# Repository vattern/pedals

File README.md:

# pedals
KiCad layouts for pedals

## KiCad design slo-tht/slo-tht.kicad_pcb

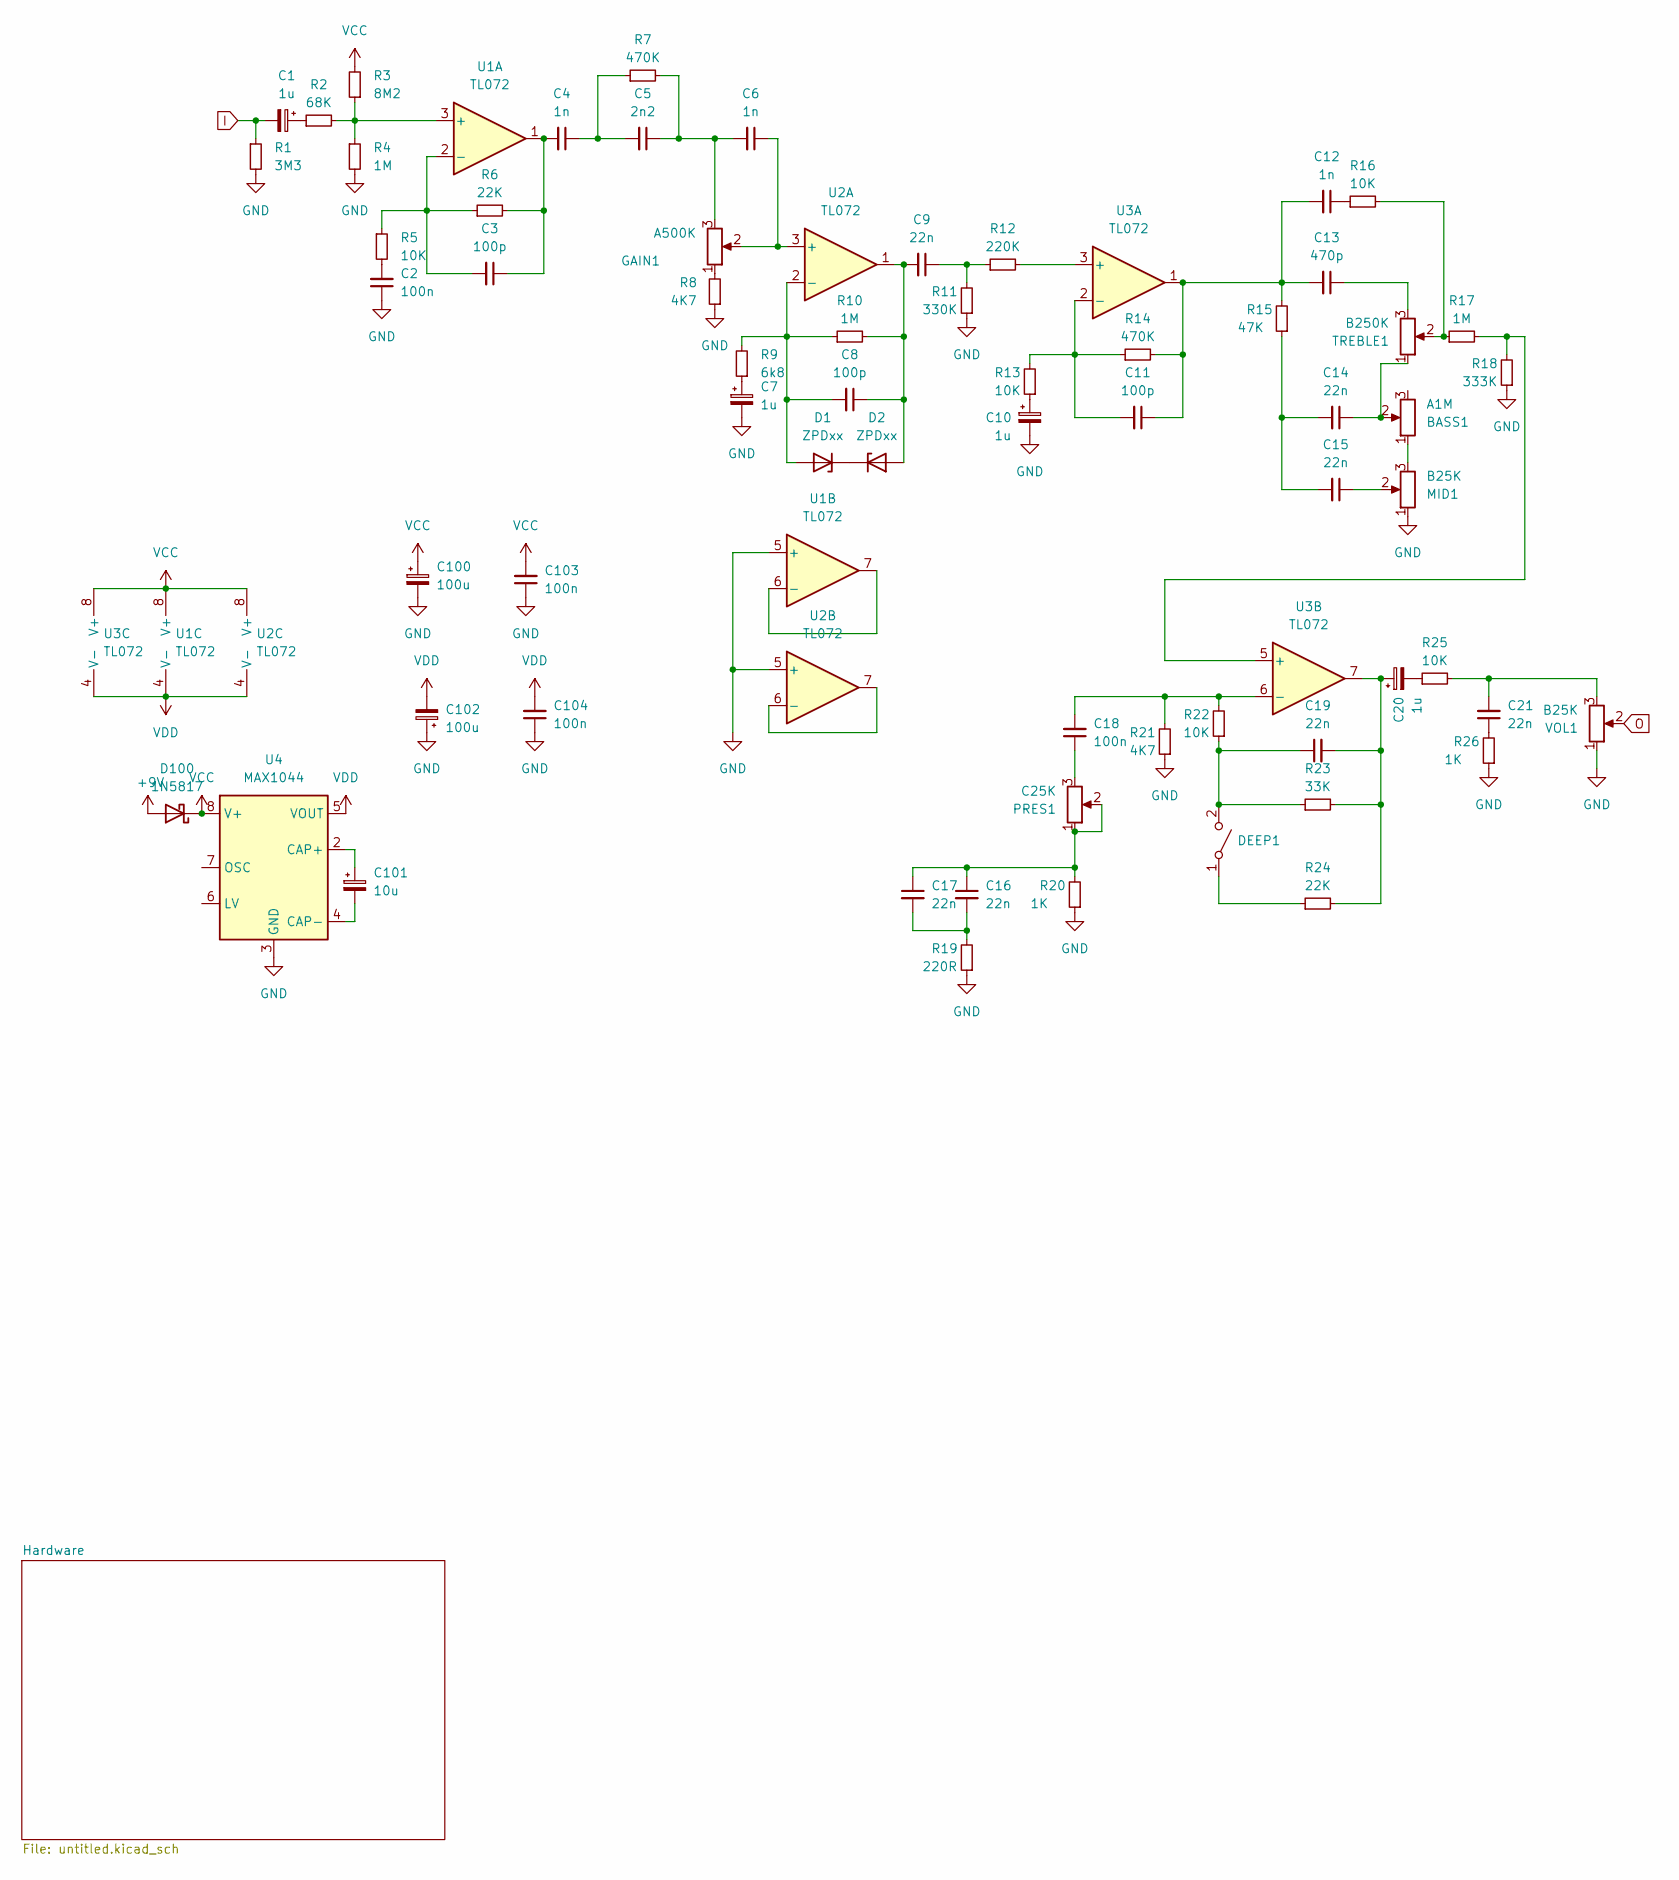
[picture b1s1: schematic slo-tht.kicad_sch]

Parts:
BASS1: A1M; Potentiometer_Alpha_RD901F-40-00D_Single_Vertical_copy
C1, C7, C10, C20: 1u; CP_Radial_D5.0mm_P2.50mm; JLCC C445065
C2, C18, C103, C104: 100n; C_Rect_L7.0mm_W2.5mm_P5.00mm; JLCC C531430
C3, C8, C11: 100p; C_Rect_L7.0mm_W2.5mm_P5.00mm; JLCC C1790
C4, C6, C12: 1n; C_Rect_L7.0mm_W2.5mm_P5.00mm; JLCC C1791
C5: 2n2; C_Rect_L7.0mm_W2.5mm_P5.00mm; JLCC C28260
C9, C14, C15, C16, C17, C19, C21: 22n; C_Rect_L7.0mm_W2.5mm_P5.00mm; JLCC C77069
C13: 470p; C_Rect_L7.0mm_W2.5mm_P5.00mm; JLCC C76630
C100, C102: 100u; CP_Radial_D8.0mm_P2.50mm; JLCC C178548
C101: 10u; CP_Radial_D5.0mm_P2.50mm; JLCC C128456
D1, D2: ZPDxx; D_DO-34_SOD68_P7.62mm_Horizontal
D100: 1N5817; D_DO-34_SOD68_P7.62mm_Horizontal; LCSC C727113
DEEP1: SW_Toggle_Blue_wSlots
GAIN1: A500K; Potentiometer_Alpha_RD901F-40-00D_Single_Vertical_copy
MID1: B25K; Potentiometer_Alpha_RD901F-40-00D_Single_Vertical_copy
PRES1: C25K; Potentiometer_Alpha_RD901F-40-00D_Single_Vertical_copy
R1: 3M3; R_Axial_DIN0204_L3.6mm_D1.6mm_P7.62mm_Horizontal; LCSC C137436
R2: 68K; R_Axial_DIN0204_L3.6mm_D1.6mm_P7.62mm_Horizontal; LCSC C17801
R3: 8M2; R_Axial_DIN0204_L3.6mm_D1.6mm_P7.62mm_Horizontal; LCSC C141694
R4: 1M; R_Axial_DIN0204_L3.6mm_D1.6mm_P7.62mm_Horizontal; JLCC C17514
R5, R13, R16, R22, R25: 10K; R_Axial_DIN0204_L3.6mm_D1.6mm_P7.62mm_Horizontal; LCSC C17414
R6, R24: 22K; R_Axial_DIN0204_L3.6mm_D1.6mm_P7.62mm_Horizontal; LCSC C17560
R7, R14: 470K; R_Axial_DIN0204_L3.6mm_D1.6mm_P7.62mm_Horizontal
R8, R21: 4K7; R_Axial_DIN0204_L3.6mm_D1.6mm_P7.62mm_Horizontal
R9: 6k8; R_Axial_DIN0204_L3.6mm_D1.6mm_P7.62mm_Horizontal
R10, R17: 1M; R_Axial_DIN0204_L3.6mm_D1.6mm_P7.62mm_Horizontal; LCSC C17514
R11: 330K; R_Axial_DIN0204_L3.6mm_D1.6mm_P7.62mm_Horizontal
R12: 220K; R_Axial_DIN0204_L3.6mm_D1.6mm_P7.62mm_Horizontal
R15: 47K; R_Axial_DIN0204_L3.6mm_D1.6mm_P7.62mm_Horizontal
R18: 333K; R_Axial_DIN0204_L3.6mm_D1.6mm_P7.62mm_Horizontal
R19: 220R; R_Axial_DIN0204_L3.6mm_D1.6mm_P7.62mm_Horizontal
R20: 1K; R_Axial_DIN0204_L3.6mm_D1.6mm_P7.62mm_Horizontal; JLCC C17513
R23: 33K; R_Axial_DIN0204_L3.6mm_D1.6mm_P7.62mm_Horizontal
R26: 1K; R_Axial_DIN0204_L3.6mm_D1.6mm_P7.62mm_Horizontal; LCSC C17513
TREBLE1: B250K; Potentiometer_Alpha_RD901F-40-00D_Single_Vertical_copy
U1, U2, U3: TL072; DIP-8_W7.62mm
U4: MAX1044; DIP-8_W7.62mm; JLCC C7028
VOL1: B25K; Potentiometer_Alpha_RD901F-40-00D_Single_Vertical_copy

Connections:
+9V: D100.2 (A); also elsewhere on the board
GND: C2.1, C7.2, C10.2, C100.2, C102.1, C103.1, C104.1, MID1.1, R1.2, R4.2, R8.1, R11.1, R18.1, R19.1, R20.1, R21.1, R26.1, U1.5 (+), U2.5 (+), U4.3 (GND), VOL1.1; also elsewhere on the board
I: C1.2, R1.1; also elsewhere on the board
unnamed: BASS1.1, MID1.3
unnamed: BASS1.2, C14.1, TREBLE1.1
unnamed: C1.1, R2.1
unnamed: C2.2, R5.2
unnamed: C3.1, C4.2, R6.2, U1.1
unnamed: C4.1, C5.2, R7.1
unnamed: C5.1, C6.2, GAIN1.3, R7.2
unnamed: C7.1, R9.1
unnamed: C9.1, R11.2, R12.1
unnamed: C10.1, R13.1
unnamed: C11.1, C12.2, C13.2, R14.2, R15.2, U3.1
unnamed: C12.1, R16.1
unnamed: C13.1, TREBLE1.3
unnamed: C14.2, C15.2, R15.1
unnamed: C15.1, MID1.2
unnamed: C16.1, C17.1, PRES1.1, PRES1.2, R20.2
unnamed: C16.2, C17.2, R19.2
unnamed: C18.1, PRES1.3
unnamed: C19.2, C20.1, R23.2, R24.2, U3.7
unnamed: C20.2, R25.1
unnamed: C21.1, R26.2
unnamed: C21.2, R25.2, VOL1.3
unnamed: C8.2, D1.2 (A), R9.2, R10.1, U2.2 (-)
unnamed: D1.1 (K), D2.1 (K)
unnamed: C8.1, C9.2, D2.2 (A), R10.2, U2.1
unnamed: DEEP1.1 (A), R24.1
unnamed: C19.1, DEEP1.2 (B), R22.1, R23.1
unnamed: GAIN1.1, R8.2
unnamed: R16.2, R17.1, TREBLE1.2
unnamed: R2.2, R3.1, R4.1, U1.3 (+)
unnamed: C3.2, R5.1, R6.1, U1.2 (-)
unnamed: U1.6 (-), U1.7
unnamed: C6.1, GAIN1.2, U2.3 (+)
unnamed: U2.6 (-), U2.7
unnamed: R12.2, U3.3 (+)
unnamed: C11.2, R13.2, R14.1, U3.2 (-)
unnamed: R17.2, R18.2, U3.5 (+)
unnamed: C18.2, R21.2, R22.2, U3.6 (-)
unnamed: C101.1, U4.2 (CAP+)
unnamed: C101.2, U4.4 (CAP-)
O: VOL1.2; also elsewhere on the board
VCC: C100.1, C103.2, D100.1 (K), R3.2, U1.8 (V+), U2.8 (V+), U3.8 (V+), U4.8 (V+)
VDD: C102.2, C104.2, U1.4 (V-), U2.4 (V-), U3.4 (V-), U4.5 (VOUT)

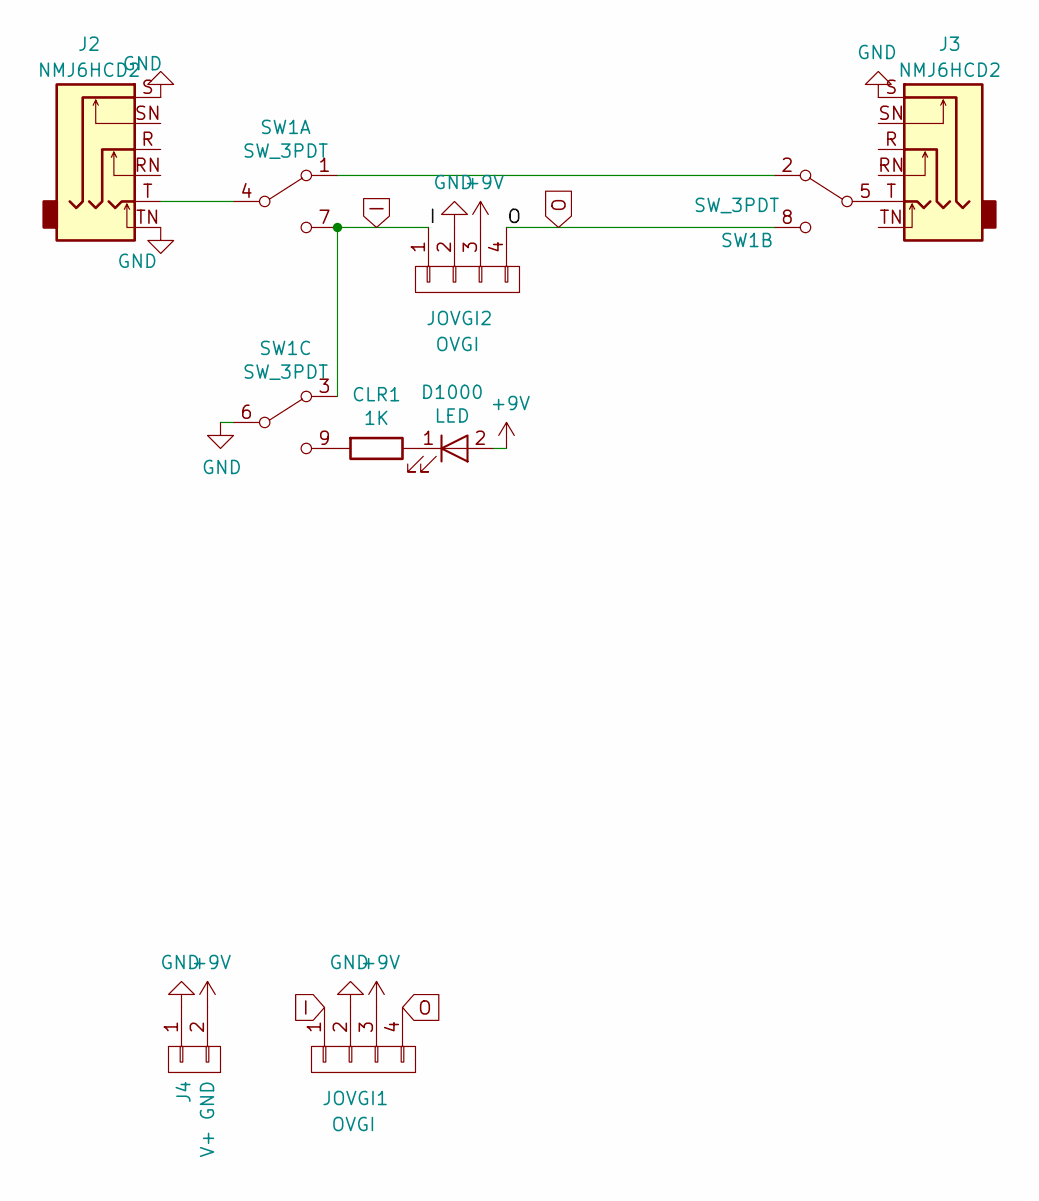
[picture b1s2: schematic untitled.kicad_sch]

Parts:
CLR1: 1K; R_Axial_DIN0204_L3.6mm_D1.6mm_P7.62mm_Horizontal
D1000: LED; LED-5MM
J2, J3: NMJ6HCD2; Jack_6.35mm_Neutrik_NMJ6HCD2_Horizontal
J4: V+ GND; PinHeader_1x02_P2.54mm_Vertical
JOVGI1, JOVGI2: OVGI; Pin_Header_Straight_1x04_Pitch2.54mm
SW1: SW_3PDT; 3PDT-Footswitch

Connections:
+9V: D1000.2 (A), J4.2, JOVGI1.3, JOVGI2.3; also elsewhere on the board
GND: J2.S, J2.TN, J3.S, J4.1, JOVGI1.2, JOVGI2.2, SW1.6 (B); also elsewhere on the board
I: JOVGI1.1, JOVGI2.1, SW1.3 (A), SW1.7 (C); also elsewhere on the board
unnamed: CLR1.1, D1000.1 (K)
unnamed: SW1.1 (A), SW1.2 (A)
unnamed: J2.T, SW1.4 (B)
unnamed: J3.T, SW1.5 (B)
unnamed: CLR1.2, SW1.9 (C)
O: JOVGI1.4, JOVGI2.4, SW1.8 (C); also elsewhere on the board

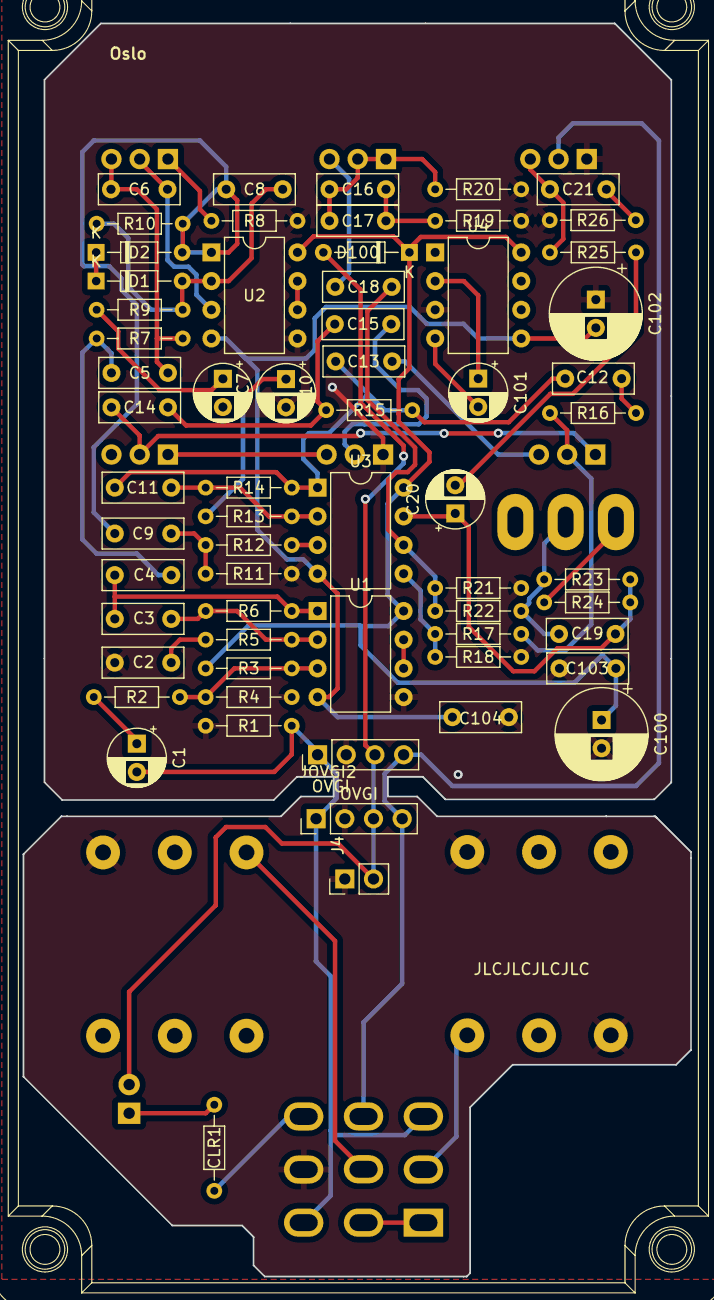
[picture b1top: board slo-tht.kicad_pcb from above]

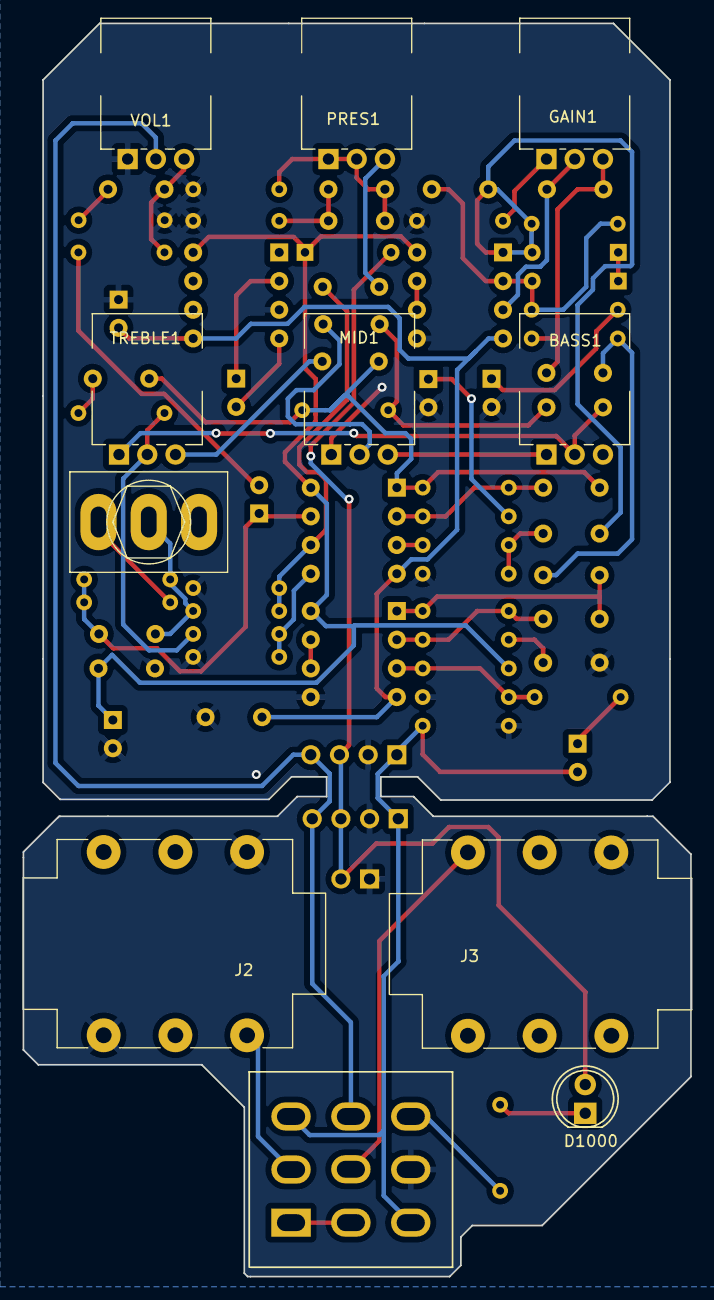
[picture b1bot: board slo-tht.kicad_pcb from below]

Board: 2 copper layers, 59.1 x 110.9 mm, 74 parts (11 on the bottom side), 51 nets.

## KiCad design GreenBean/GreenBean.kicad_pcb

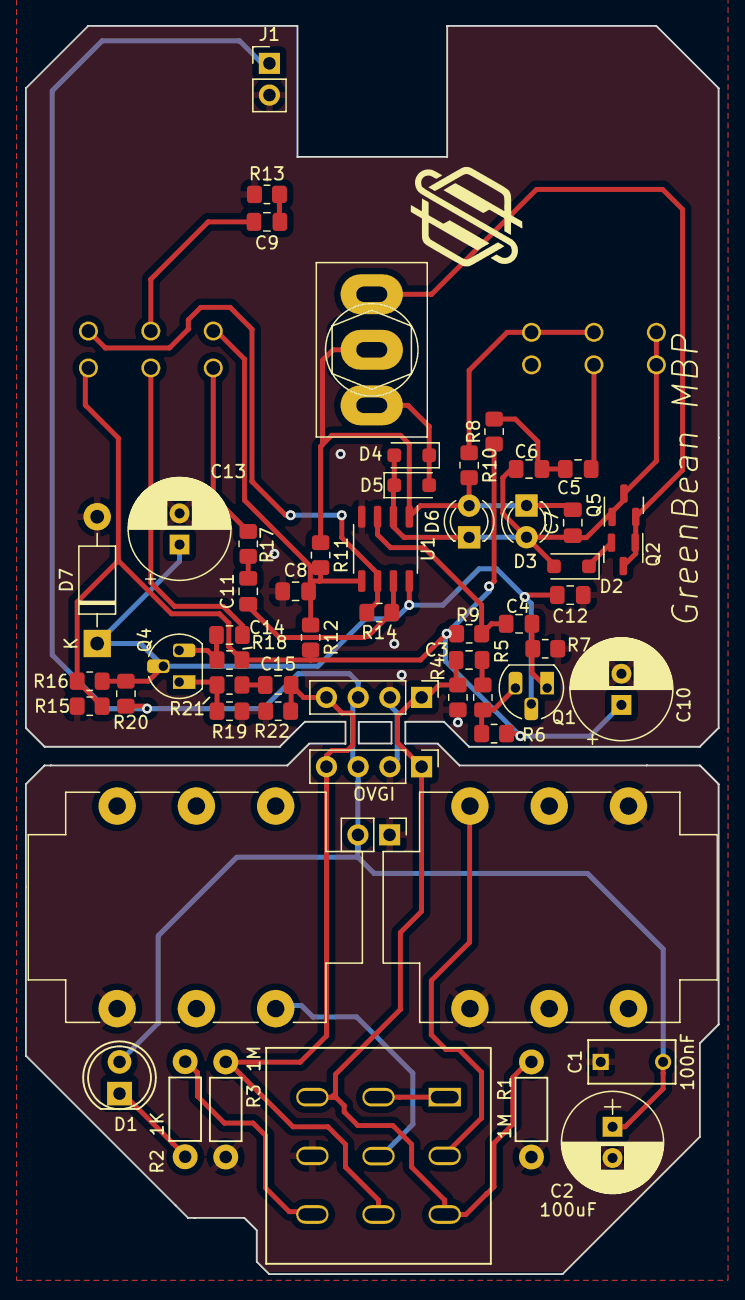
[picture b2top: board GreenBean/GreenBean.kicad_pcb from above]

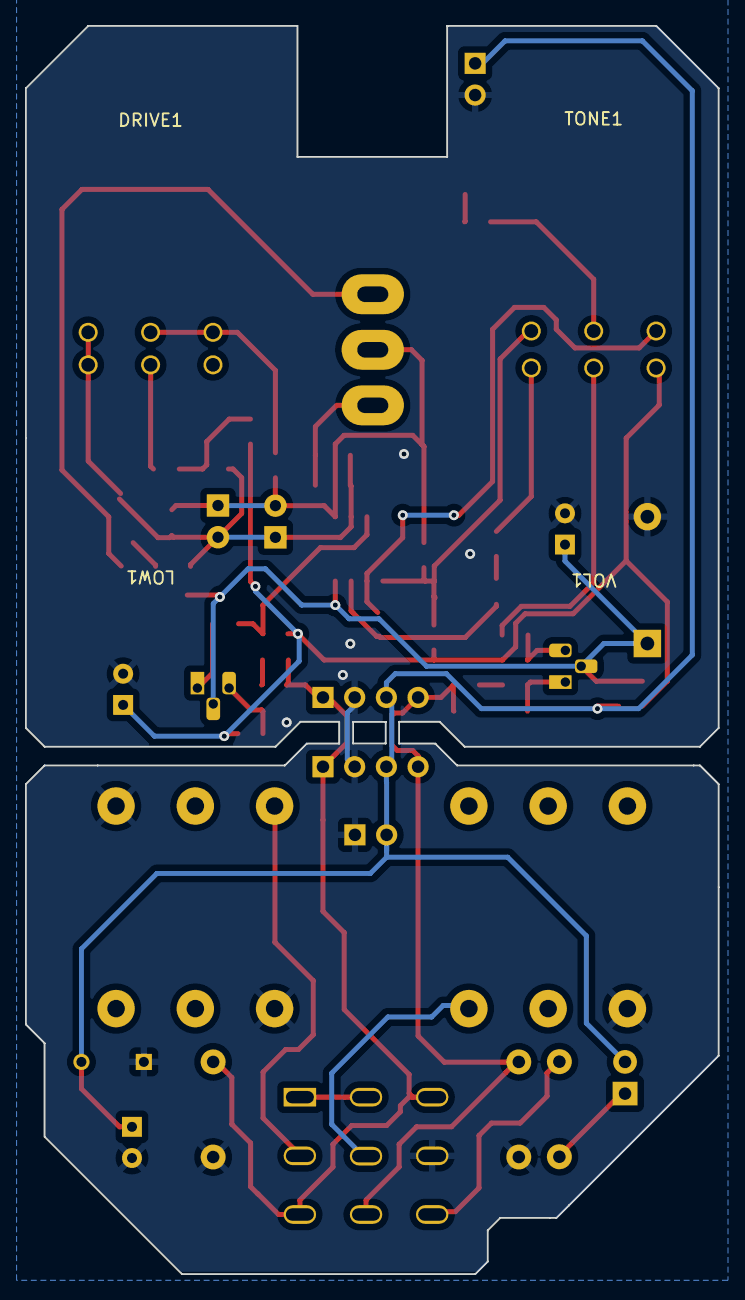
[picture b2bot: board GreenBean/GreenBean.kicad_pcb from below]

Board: 2 copper layers, 55.5 x 100.0 mm, 62 parts (4 on the bottom side), 34 nets.

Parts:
C1: 100nF; C_Rect_L7_W3.5_P5
C2, C13: 100uF; CP_Radial_D8.0mm_P2.50mm
C3: 20n; C_0805_2012Metric_Pad1.18x1.45mm_HandSolder
C4, C11, C15: 1u; C_0805_2012Metric_Pad1.18x1.45mm_HandSolder
C5: 150n; C_0805_2012Metric_Pad1.18x1.45mm_HandSolder
C6: 47n; C_0805_2012Metric_Pad1.18x1.45mm_HandSolder
C7: 51p; C_0805_2012Metric_Pad1.18x1.45mm_HandSolder
C8, C9, C12: 220n; C_0805_2012Metric_Pad1.18x1.45mm_HandSolder
C10: 10uF; CP_Radial_D8.0mm_P2.50mm
C14: 100n; C_0805_2012Metric_Pad1.18x1.45mm_HandSolder
D1: LED; LED-5MM
D2: BAT41; D_SOD-123F
D3, D6: LED; LED_D3.0mm
D4, D5: 1N914; D_SOD-123F
D7: 1N4001; D_DO-41_SOD81_P10.16mm_Horizontal
DRIVE1: 500KA; Potentiometer_ALPHA_RV16106N
J1, J4: V+ GND; PinHeader_1x02_P2.54mm_Vertical
J2, J3: NMJ6HCD2; Jack_6.35mm_Neutrik_NMJ6HCD2_Horizontal
JOVGI1, JOVGI2: OVGI; Pin_Header_Straight_1x04_Pitch2.54mm
LOW1: 20KB; Potentiometer_ALPHA_RV16106N
N1: Housing; 1590B
Q1, Q4: 2SC1815; TO-92L_HandSolder
Q2, Q5: 2N7002; SOT-23
R1, R3: 1M; Resistor_Horizontal_RM7mm
R2: 1K; Resistor_Horizontal_RM7mm
R4: 1M; R_0805_2012Metric_Pad1.20x1.40mm_HandSolder
R5, R11, R14, R17: 1k; R_0805_2012Metric_Pad1.20x1.40mm_HandSolder
R6, R18: 510k; R_0805_2012Metric_Pad1.20x1.40mm_HandSolder
R7, R9, R12, R15, R16, R19, R22: 10k; R_0805_2012Metric_Pad1.20x1.40mm_HandSolder
R8: 4k7; R_0805_2012Metric_Pad1.20x1.40mm_HandSolder
R10: 51k; R_0805_2012Metric_Pad1.20x1.40mm_HandSolder
R13: 220R; R_0805_2012Metric_Pad1.20x1.40mm_HandSolder
R20: 47R; R_0805_2012Metric_Pad1.20x1.40mm_HandSolder
R21: 100R; R_0805_2012Metric_Pad1.20x1.40mm_HandSolder
SW1: SW_3PDT; 3PDT-Footswitch
SW2: SW_SPDT; SW_Toggle_Blue_wSlots
TONE1: 20KB; Potentiometer_ALPHA_RV16106N
U1: RC4558; SO-8_3.9x4.9mm_P1.27mm
VOL1: 100KB; Potentiometer_ALPHA_RV16106N

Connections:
+9V: C1.2, C2.1, D1.2 (A), J1.1, J4.2, JOVGI1.3, JOVGI2.3, R20.2
A: C6.2, C7.1, D2.2 (A), D3.2 (A), D4.2 (A), D5.1 (K), D6.1 (K), DRIVE1.1, LOW1.3, Q5.1 (G), Q5.3 (D), U1.2 (-)
B: C7.2, D3.1 (K), D6.2 (A), R10.2, R11.1, SW2.2, U1.1
GND: C1.1, C2.2, C8.1, C10.2, C12.1, C13.2, D7.2 (A), J1.2, J2.S, J2.TN, J3.S, J4.1, JOVGI1.2, JOVGI2.2, R1.2, R3.2, R4.1, R7.1, R13.1, R15.1, R19.1, R22.1, SW1.6 (B), U1.4 (V-)
I: C3.1, JOVGI1.1, JOVGI2.1, R1.1, R4.2, SW1.3 (A), SW1.7 (C)
unnamed: C3.2, R5.2
unnamed: C5.1, C6.1, R8.2
unnamed: C5.2, LOW1.2
unnamed: C9.1, R13.2
unnamed: C9.2, TONE1.2
unnamed: C11.1, R14.2, U1.7
unnamed: C11.2, R17.1
unnamed: C14.1, VOL1.2
unnamed: C15.1, R21.2
unnamed: D1.1 (K), R2.1
unnamed: D2.1 (K), Q2.2 (S)
unnamed: D4.1 (K), D5.2 (A), SW2.1
unnamed: DRIVE1.2, DRIVE1.3, R10.1
unnamed: Q1.3 (B), R5.1, R6.1
unnamed: C4.1, Q1.1 (E), R7.2
unnamed: Q2.1 (G), Q2.3 (D), Q5.2 (S), SW2.3
unnamed: C14.2, Q4.3 (B), R18.1
unnamed: Q4.1 (E), R19.2, R21.1
unnamed: R17.2, VOL1.3
unnamed: SW1.1 (A), SW1.2 (A)
unnamed: J2.T, SW1.4 (B)
unnamed: J3.T, SW1.5 (B)
unnamed: R2.2, SW1.9 (C)
unnamed: C4.2, R9.1, U1.3 (+)
unnamed: C8.2, R11.2, R12.1, TONE1.1, U1.5 (+)
unnamed: R14.1, TONE1.3, U1.6 (-)
O: C15.2, JOVGI1.4, JOVGI2.4, R3.1, R22.2, SW1.8 (C)
VB: C10.1, R6.2, R8.1, R9.2, R12.2, R15.2, R16.1, R18.2, VOL1.1
VC: C12.2, C13.1, D7.1 (K), Q1.2 (C), Q4.2 (C), R16.2, R20.1, U1.8 (V+)

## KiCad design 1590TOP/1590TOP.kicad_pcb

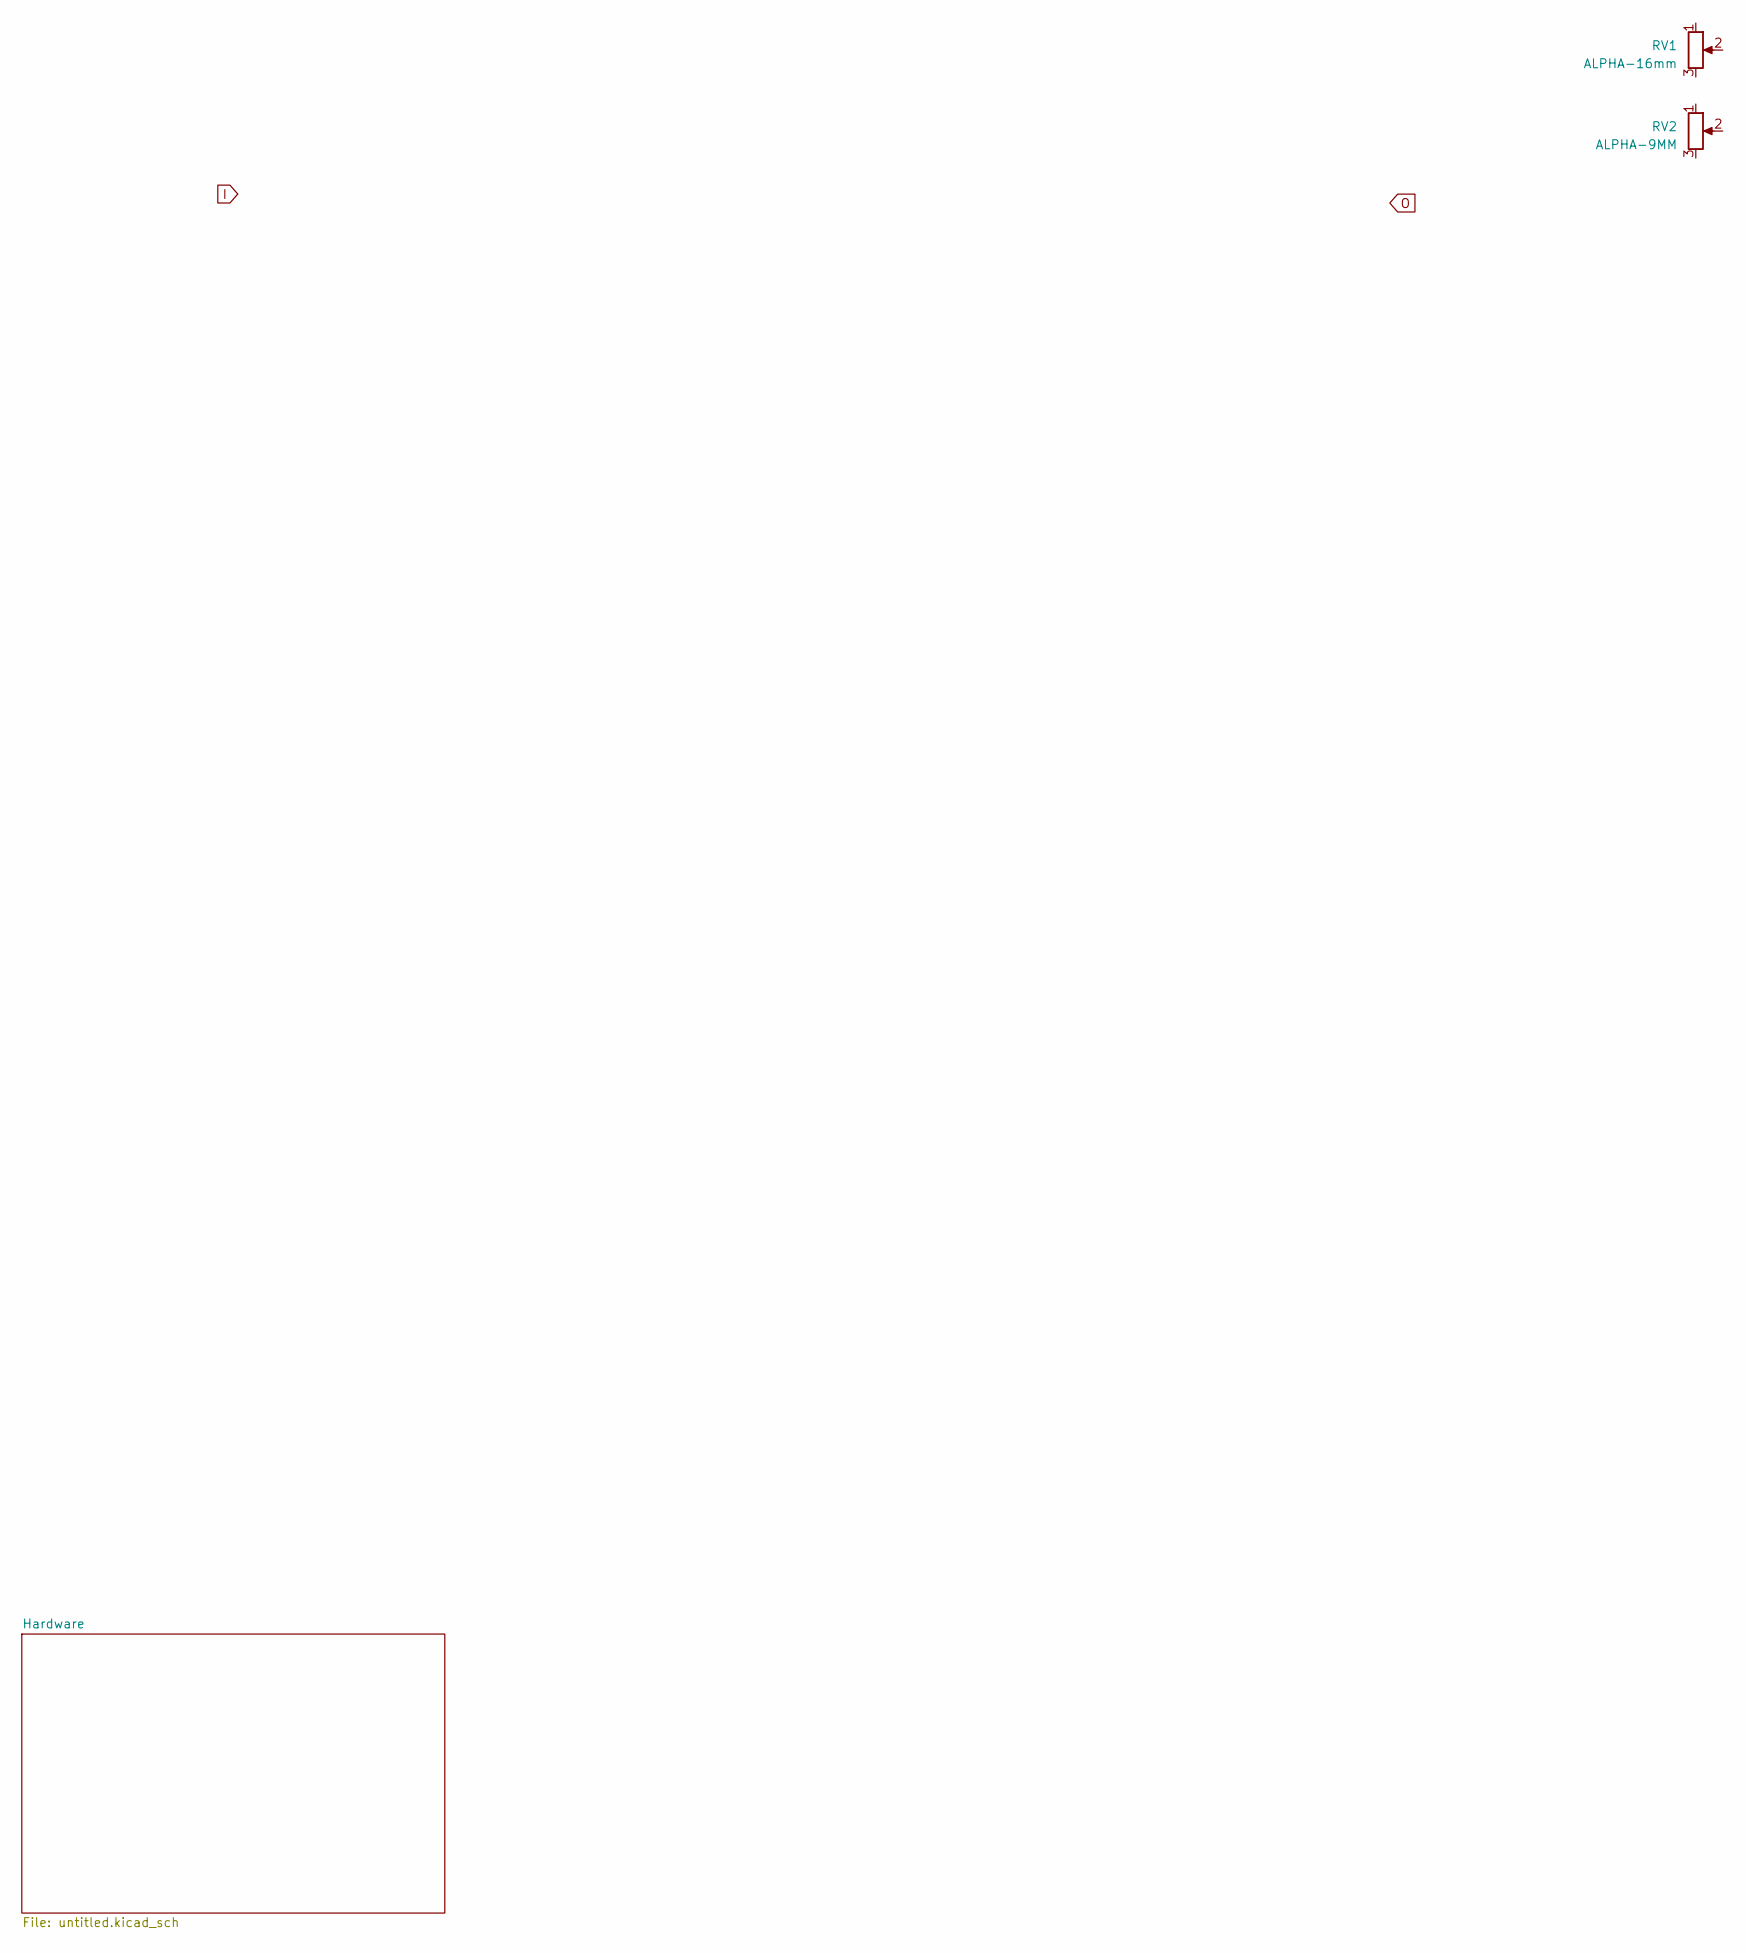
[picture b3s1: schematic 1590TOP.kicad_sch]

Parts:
RV1: ALPHA-16mm; Potentiometer_ALPHA_RV16106N
RV2: ALPHA-9MM; Potentiometer_Alpha_RD901F-40-00D_Single_Vertical

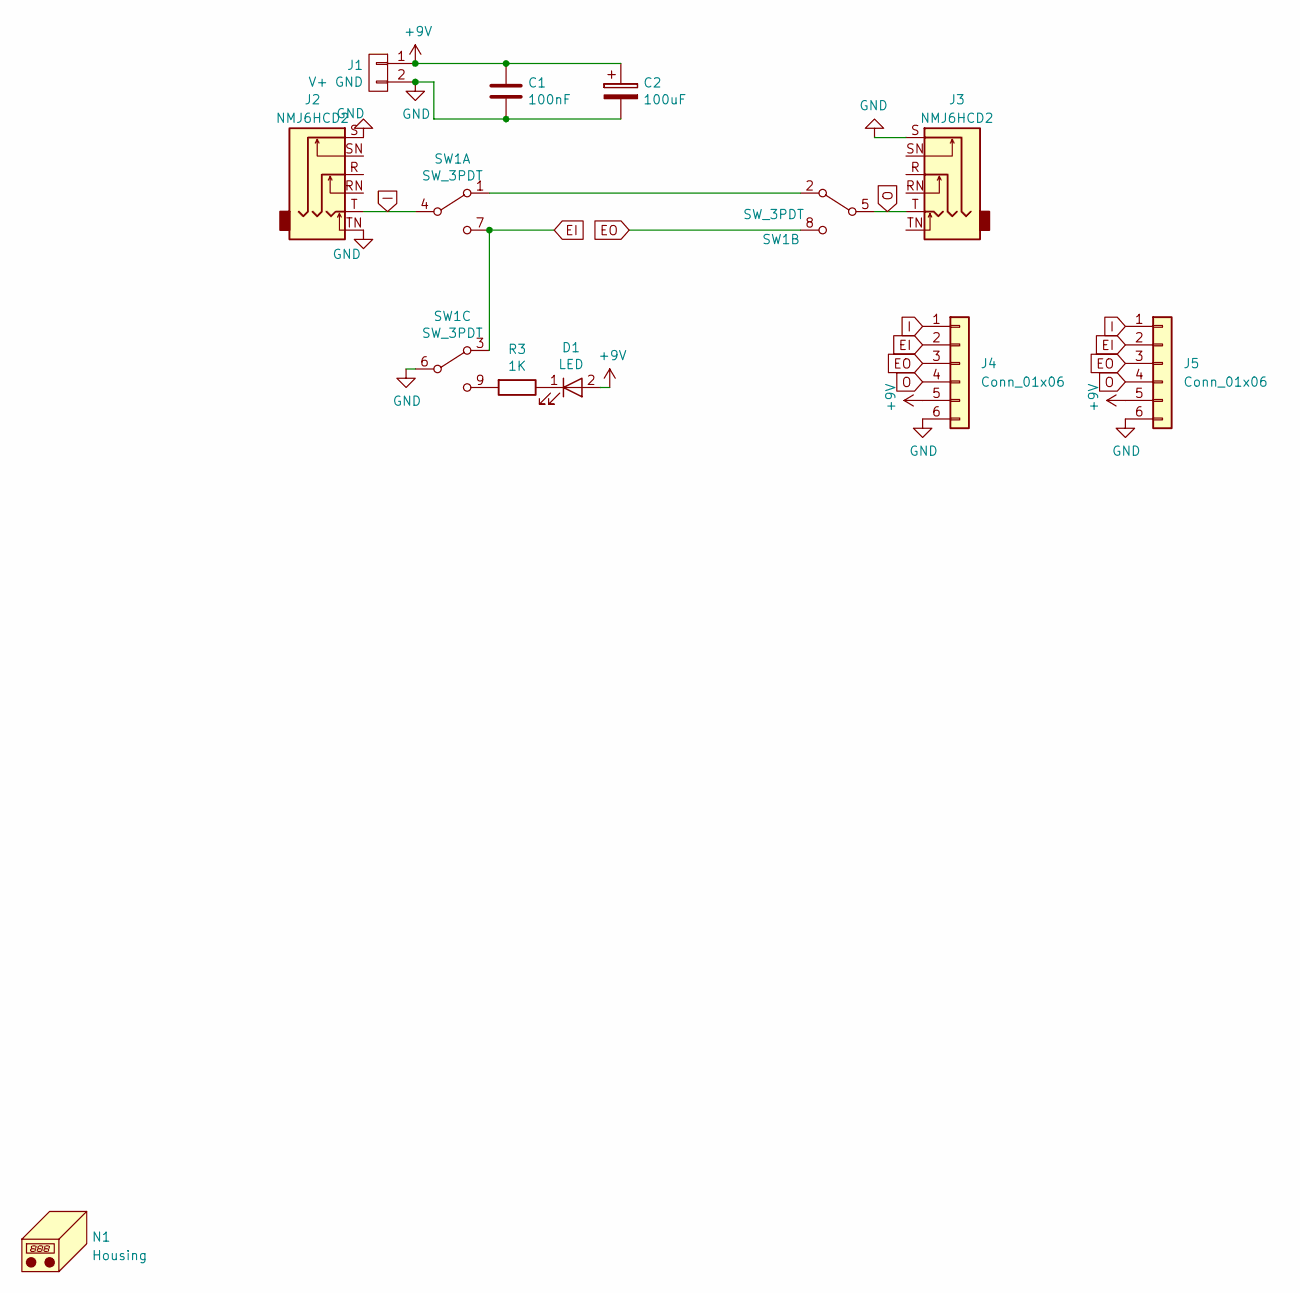
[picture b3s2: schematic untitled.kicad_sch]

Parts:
C1: 100nF; C_Rect_L7_W3.5_P5
C2: 100uF; CP_Radial_D8.0mm_P2.50mm
D1: LED; LED-5MM
J1: V+ GND; PinHeader_1x02_P2.54mm_Vertical
J2, J3: NMJ6HCD2; Jack_6.35mm_Neutrik_NMJ6HCD2_Horizontal
J4, J5: Conn_01x06; PinHeader_1x06_P2.54mm_Vertical
N1: Housing; 1590B
R3: 1K; Resistor_Horizontal_RM7mm
SW1: SW_3PDT; 3PDT-Footswitch

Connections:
+9V: C1.2, C2.1, D1.2 (A), J1.1, J4.5, J5.5
EI: J4.2, J5.2, SW1.3 (A), SW1.7 (C)
EO: J4.3, J5.3, SW1.8 (C)
GND: C1.1, C2.2, J1.2, J2.S, J2.TN, J3.S, J4.6, J5.6, SW1.6 (B)
I: J2.T, J4.1, J5.1, SW1.4 (B)
unnamed 5: D1.1 (K); also elsewhere on the board
unnamed: SW1.1 (A), SW1.2 (A)
unnamed 7: SW1.9 (C); also elsewhere on the board
O: J3.T, J4.4, J5.4, SW1.5 (B)

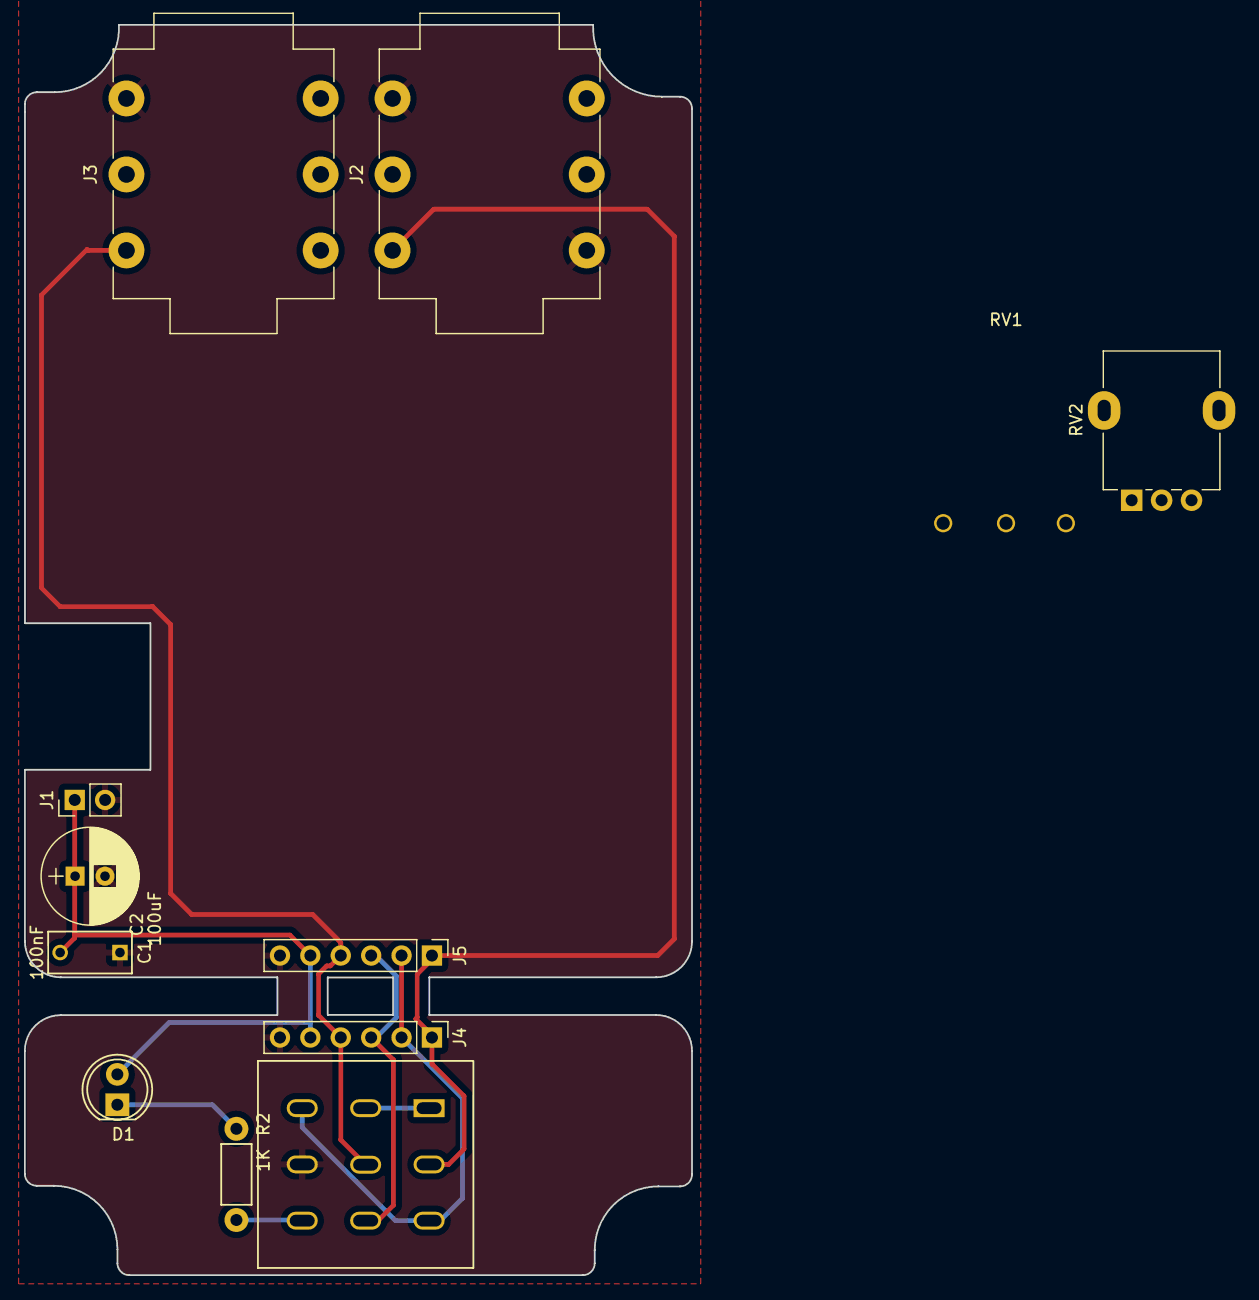
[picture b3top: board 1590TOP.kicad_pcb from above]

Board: 2 copper layers, 55.8 x 104.5 mm, 13 parts (0 on the bottom side), 9 nets.

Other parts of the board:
R2: 1K; Resistor_Horizontal_RM7mm

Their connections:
unnamed 5: R2.1; also elsewhere on the board
unnamed 7: R2.2; also elsewhere on the board
